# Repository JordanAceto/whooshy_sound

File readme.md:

# Effects pedal for making whooshy filter and phaser sweeping sounds

## This pedal accommodates various VCF plug-in boards, and contains rich modulation features.

### [SCHEMATIC](https://github.com/JordanAceto/whooshy_sound/blob/main/hardware/main_pcb/construction_docs/whooshy_sound_main_pcb_schematic.pdf)

---

### Features:
- Guitar pedal style stomp box.
- Can accept a wide variety of [filter plug-in boards](https://github.com/JordanAceto/VCF_plug_in_boards).
    - For guitars and other instrument-level signals I recommend starting with the "2164" filter plug-in boards, because these have very low noise and CV feedthrough.
    - Other plug-in boards will work for guitars, but may be a little noisier and thumpier than you wish. Try them out, they vary.
    - If you're using this in an effects loop or after a preamp, it doesn't matter as much and any of them will probably be fine.
- Manual frequency and resonance controls.
- Digitally generated LFO with morphing waveshaper, smoothly crossfades from triangle to sine to square to sample & hold.
- Analog envelope follower for when you want to quack and bwow instead of whoosh.

---

### Status of the project:

Revision | schematic | pcb layout | firmware | built and tested | safe to order boards
------|--------------|-----------|------------|---------|---------
0.1 | &#9745; | &#9745; | &#9745; | &#9745; | &#9745;

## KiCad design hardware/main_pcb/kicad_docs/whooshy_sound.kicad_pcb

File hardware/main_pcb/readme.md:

# Main PCB

## The main PCB contains:
- input and output audio buffers
- a software generated LFO
- an envelope follower
- a port which accepts various VCF plug-in boards
- power supply components

---

### PCB front view:

---

### PCB rear view:

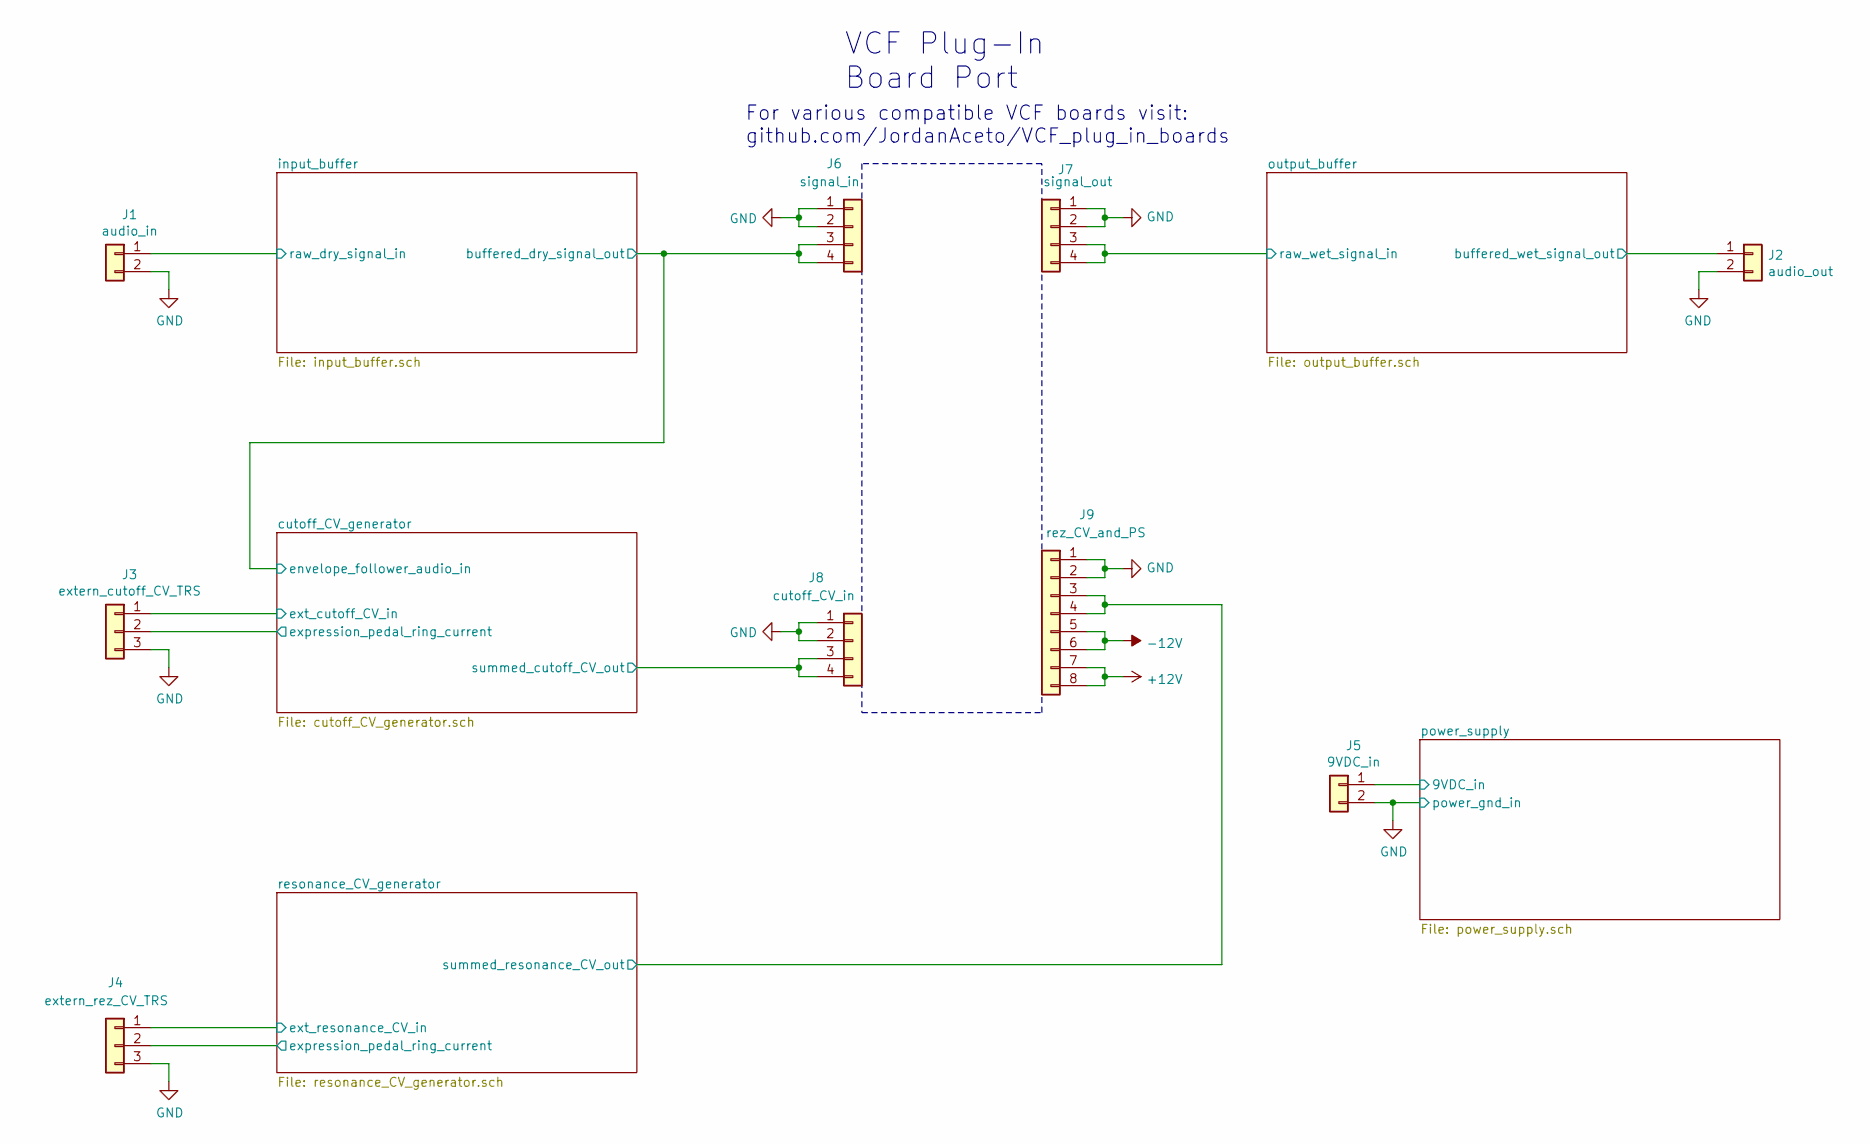
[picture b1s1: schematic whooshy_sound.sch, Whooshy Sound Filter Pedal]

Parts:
J1: audio_in; PinHeader_1x02_P2.54mm_Vertical
J2: audio_out; PinHeader_1x02_P2.54mm_Vertical
J3: extern_cutoff_CV_TRS; PinHeader_1x03_P2.54mm_Vertical
J4: extern_rez_CV_TRS; PinHeader_1x03_P2.54mm_Vertical
J5: 9VDC_in; PinHeader_1x02_P2.54mm_Vertical
J6: signal_in; PinSocket_1x04_P2.54mm_Vertical
J7: signal_out; PinSocket_1x04_P2.54mm_Vertical
J8: cutoff_CV_in; PinSocket_1x04_P2.54mm_Vertical
J9: rez_CV_and_PS; PinSocket_1x08_P2.54mm_Vertical

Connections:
+12V: J9.7, J9.8; also elsewhere on the board
-12V: J9.5, J9.6; also elsewhere on the board
/cutoff_CV_generator/expression_pedal_ring_current: J3.2; also elsewhere on the board
/cutoff_CV_generator/ext_cutoff_CV_in: J3.1; also elsewhere on the board
/cutoff_CV_generator/summed_cutoff_CV_out: J8.3, J8.4; also elsewhere on the board
/input_buffer/buffered_dry_signal_out: J6.3, J6.4; also elsewhere on the board
/input_buffer/raw_dry_signal_in: J1.1; also elsewhere on the board
/output_buffer/buffered_wet_signal_out: J2.1; also elsewhere on the board
/output_buffer/raw_wet_signal_in: J7.3, J7.4; also elsewhere on the board
/power_supply/9VDC_in: J5.1; also elsewhere on the board
/resonance_CV_generator/expression_pedal_ring_current: J4.2; also elsewhere on the board
/resonance_CV_generator/ext_resonance_CV_in: J4.1; also elsewhere on the board
/resonance_CV_generator/summed_resonance_CV_out: J9.3, J9.4; also elsewhere on the board
GND: J1.2, J2.2, J3.3, J4.3, J5.2, J6.1, J6.2, J7.1, J7.2, J8.1, J8.2, J9.1, J9.2; also elsewhere on the board

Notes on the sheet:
VCF Plug-In Board Port
For various compatible VCF boards visit: github.com/JordanAceto/VCF_plug_in_boards

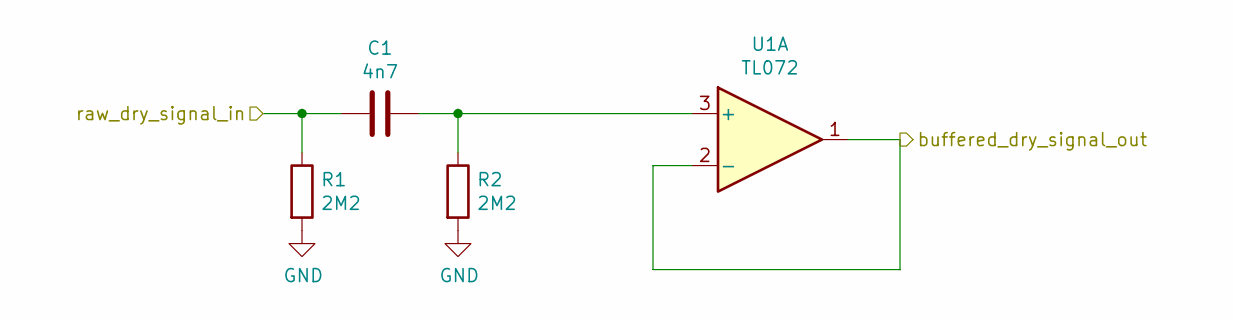
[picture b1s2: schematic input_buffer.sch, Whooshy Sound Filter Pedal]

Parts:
C1: 4n7; C_Rect_L7.0mm_W2.5mm_P5.00mm
R1, R2: 2M2; R_0805_2012Metric
U1: TL072; SOIC-8_3.9x4.9mm_P1.27mm

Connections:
/input_buffer/buffered_dry_signal_out: U1.1, U1.2 (-); also elsewhere on the board
/input_buffer/raw_dry_signal_in: C1.2, R1.1; also elsewhere on the board
GND: R1.2, R2.2; also elsewhere on the board
unnamed: C1.1, R2.1, U1.3 (+)

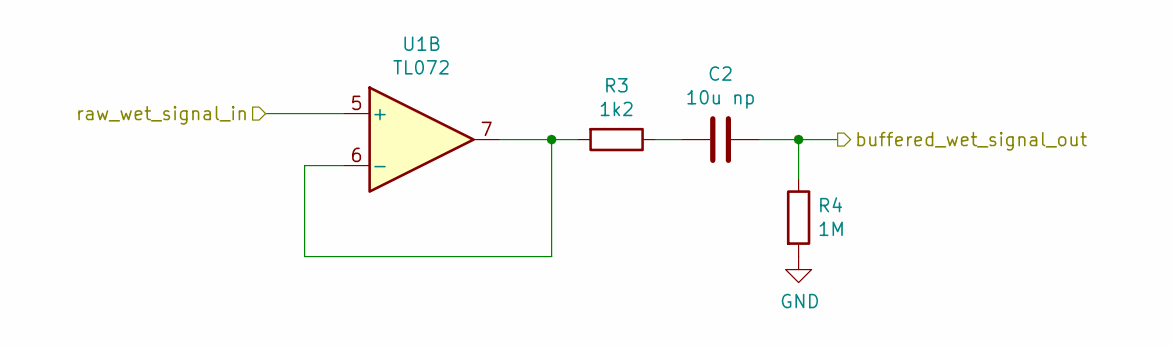
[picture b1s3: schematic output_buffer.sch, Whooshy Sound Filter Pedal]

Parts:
C2: 10u np; C_Radial_D6.3mm_H11.0mm_P2.50mm
R3: 1k2; R_0805_2012Metric
R4: 1M; R_0805_2012Metric
U1: TL072; SOIC-8_3.9x4.9mm_P1.27mm

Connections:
/output_buffer/buffered_wet_signal_out: C2.1, R4.1; also elsewhere on the board
/output_buffer/raw_wet_signal_in: U1.5 (+); also elsewhere on the board
GND: R4.2; also elsewhere on the board
unnamed: C2.2, R3.1
unnamed: R3.2, U1.6 (-), U1.7

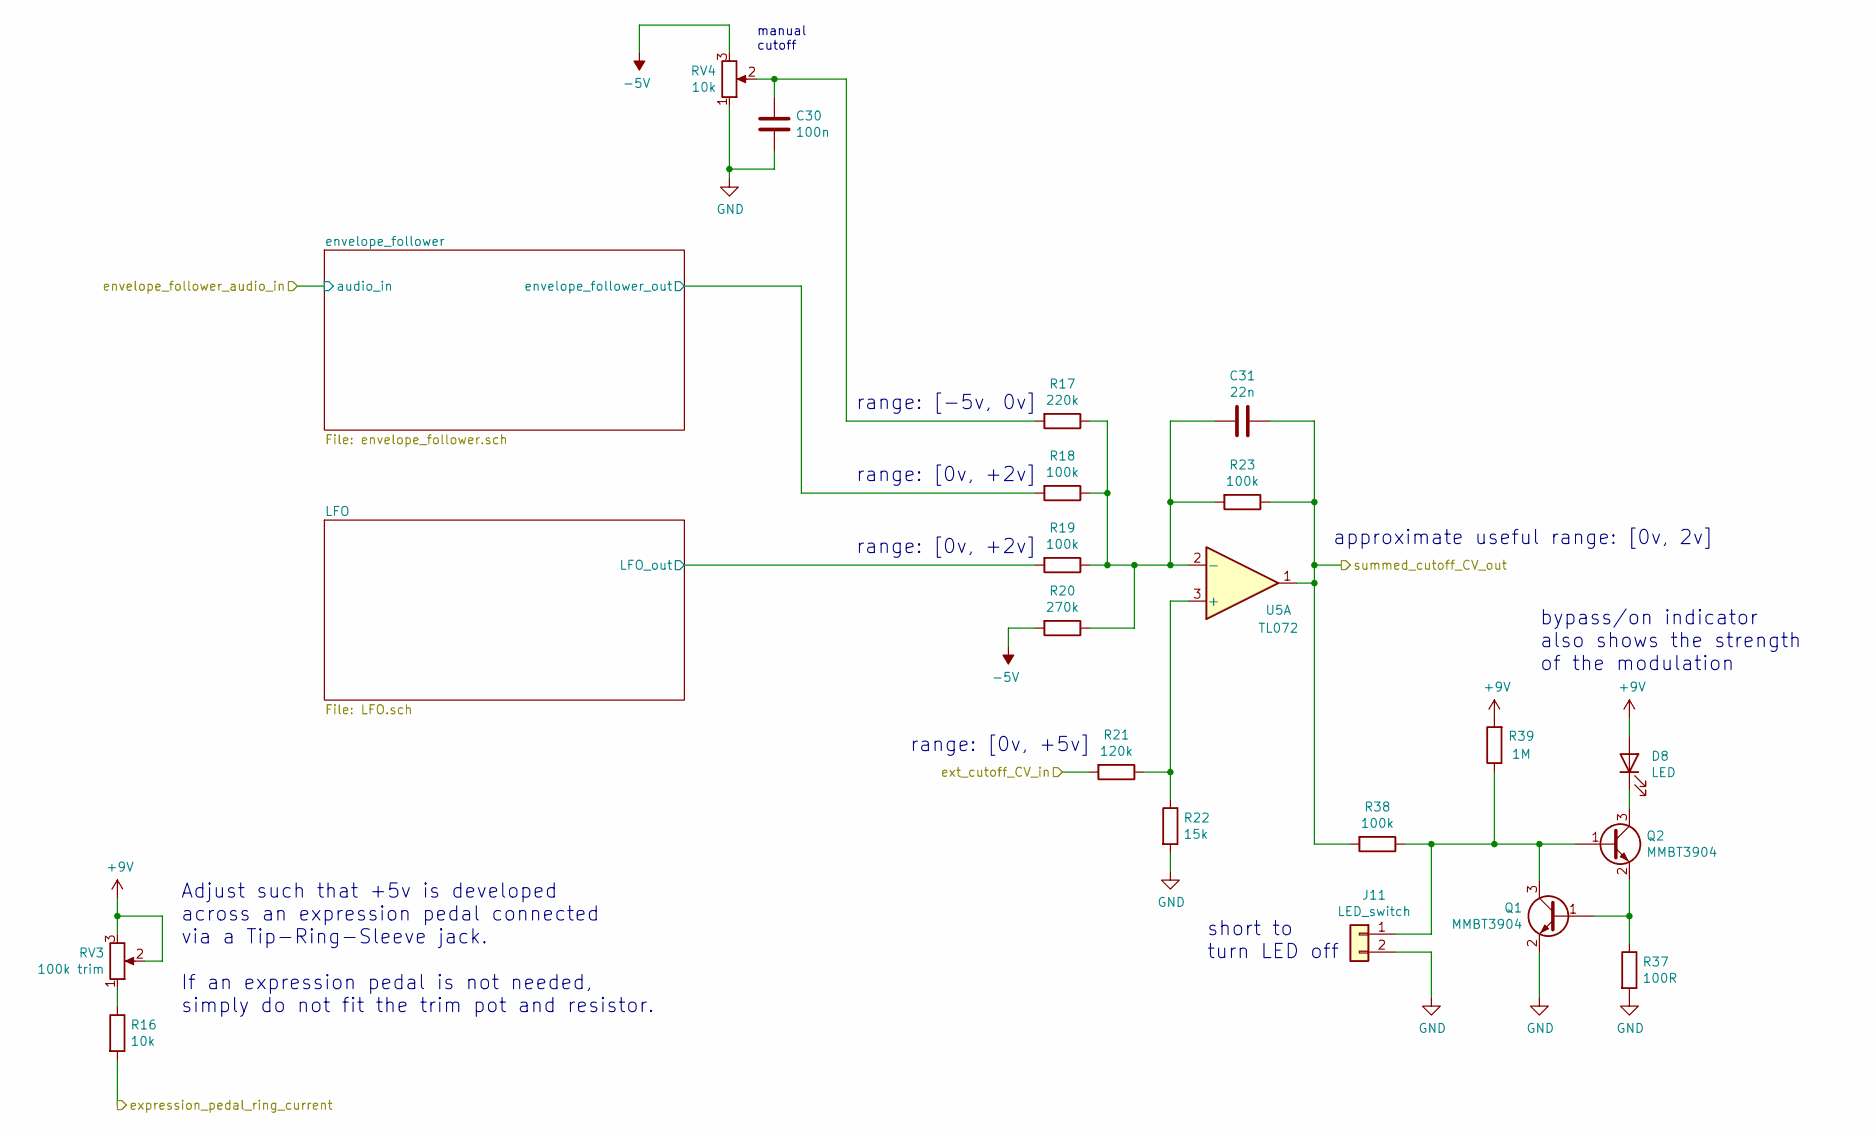
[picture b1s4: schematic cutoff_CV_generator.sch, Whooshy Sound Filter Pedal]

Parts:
C30: 100n; C_0805_2012Metric
C31: 22n; C_0805_2012Metric
D8: LED; LED_D5.0mm
J11: LED_switch; PinHeader_1x02_P2.54mm_Vertical
Q1, Q2: MMBT3904; SOT-23
R16: 10k; R_0805_2012Metric
R17: 220k; R_0805_2012Metric
R18, R19, R23, R38: 100k; R_0805_2012Metric
R20: 270k; R_0805_2012Metric
R21: 120k; R_0805_2012Metric
R22: 15k; R_0805_2012Metric
R37: 100R; R_0805_2012Metric
R39: 1M; R_0805_2012Metric
RV3: 100k trim; Potentiometer_Bourns_3296W_Vertical
RV4: 10k; Potentiometer_Alpha_RD901F-40-00D_Single_Vertical
U5: TL072; SOIC-8_3.9x4.9mm_P1.27mm

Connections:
+9V: D8.2 (A), R39.2, RV3.2, RV3.3; also elsewhere on the board
-5V: R20.2, RV4.3; also elsewhere on the board
/cutoff_CV_generator/LFO/LFO_out: R19.2; also elsewhere on the board
/cutoff_CV_generator/envelope_follower/envelope_follower_out: R18.2; also elsewhere on the board
/cutoff_CV_generator/expression_pedal_ring_current: R16.2; also elsewhere on the board
/cutoff_CV_generator/ext_cutoff_CV_in: R21.2; also elsewhere on the board
/cutoff_CV_generator/summed_cutoff_CV_out: C31.1, R23.1, R38.2, U5.1; also elsewhere on the board
GND: C30.2, J11.2, Q1.2 (E), R22.2, R37.2, RV4.1; also elsewhere on the board
unnamed: C30.1, R17.2, RV4.2
unnamed: C31.2, R17.1, R18.1, R19.1, R20.1, R23.2, U5.2 (-)
unnamed: D8.1 (K), Q2.3 (C)
unnamed: J11.1, Q1.3 (C), Q2.1 (B), R38.1, R39.1
unnamed: Q1.1 (B), Q2.2 (E), R37.1
unnamed: R16.1, RV3.1
unnamed: R21.1, R22.1, U5.3 (+)

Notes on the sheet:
range: [-5v, 0v]
range: [0v, +2v]
range: [0v, +5v]
approximate useful range: [0v, 2v]
manual cutoff
Adjust such that +5v is developed across an expression pedal connected via a Tip-Ring-Sleeve jack. If an expression pedal is not needed, simply do not fit the trim pot and resistor.
bypass/on indicator also shows the strength of the modulation
short to turn LED off

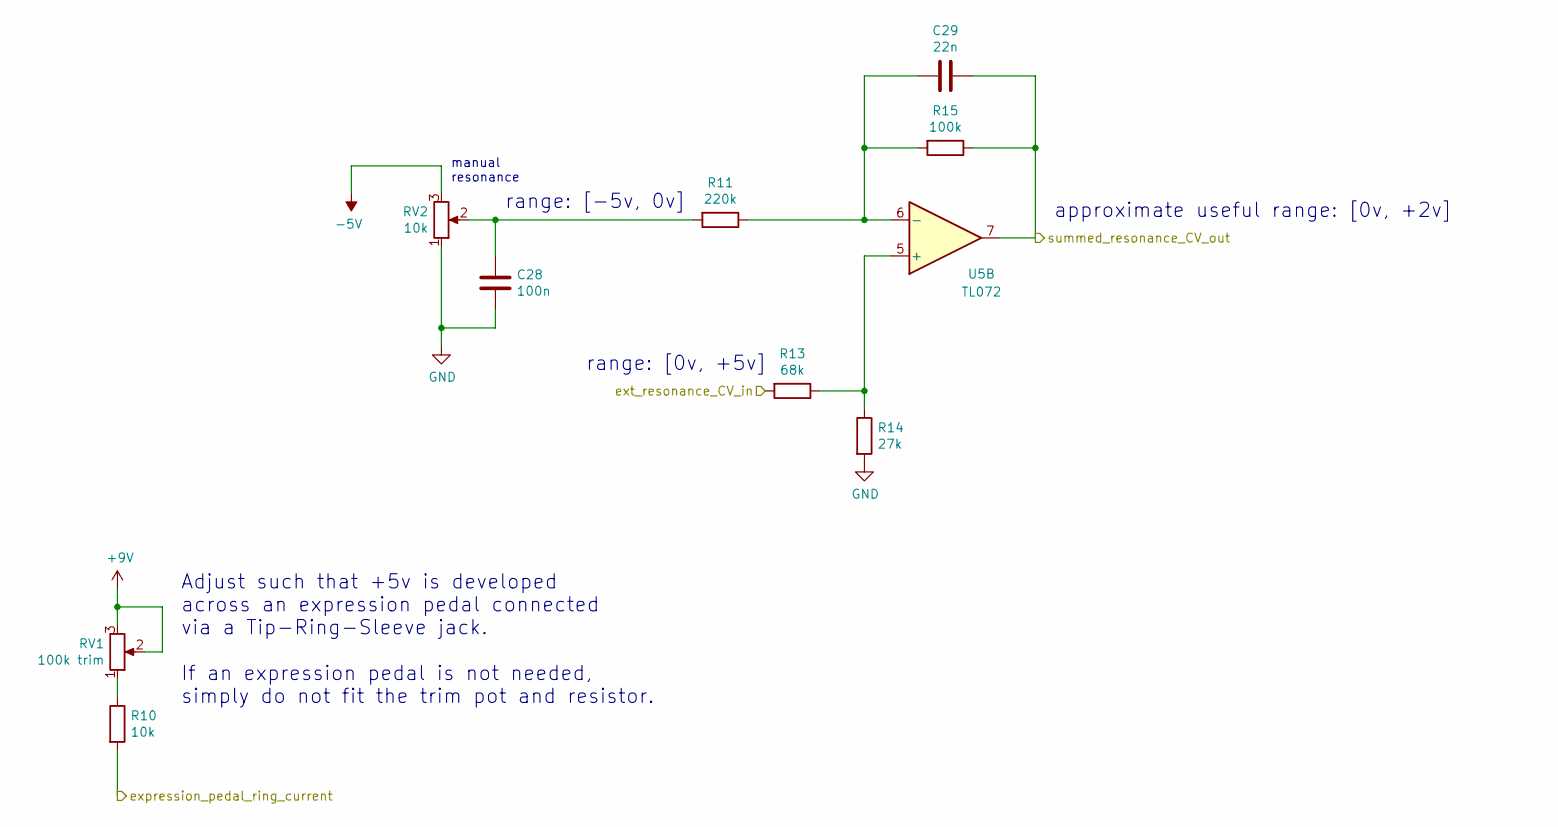
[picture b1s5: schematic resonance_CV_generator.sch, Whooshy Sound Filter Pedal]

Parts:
C28: 100n; C_0805_2012Metric
C29: 22n; C_0805_2012Metric
R10: 10k; R_0805_2012Metric
R11: 220k; R_0805_2012Metric
R13: 68k; R_0805_2012Metric
R14: 27k; R_0805_2012Metric
R15: 100k; R_0805_2012Metric
RV1: 100k trim; Potentiometer_Bourns_3296W_Vertical
RV2: 10k; Potentiometer_Alpha_RD901F-40-00D_Single_Vertical
U5: TL072; SOIC-8_3.9x4.9mm_P1.27mm

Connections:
+9V: RV1.2, RV1.3; also elsewhere on the board
-5V: RV2.3; also elsewhere on the board
/resonance_CV_generator/expression_pedal_ring_current: R10.2; also elsewhere on the board
/resonance_CV_generator/ext_resonance_CV_in: R13.2; also elsewhere on the board
/resonance_CV_generator/summed_resonance_CV_out: C29.1, R15.1, U5.7; also elsewhere on the board
GND: C28.2, R14.2, RV2.1; also elsewhere on the board
unnamed: C28.1, R11.2, RV2.2
unnamed: C29.2, R11.1, R15.2, U5.6 (-)
unnamed: R10.1, RV1.1
unnamed: R13.1, R14.1, U5.5 (+)

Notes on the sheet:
approximate useful range: [0v, +2v]
range: [-5v, 0v]
range: [0v, +5v]
Adjust such that +5v is developed across an expression pedal connected via a Tip-Ring-Sleeve jack. If an expression pedal is not needed, simply do not fit the trim pot and resistor.
manual resonance

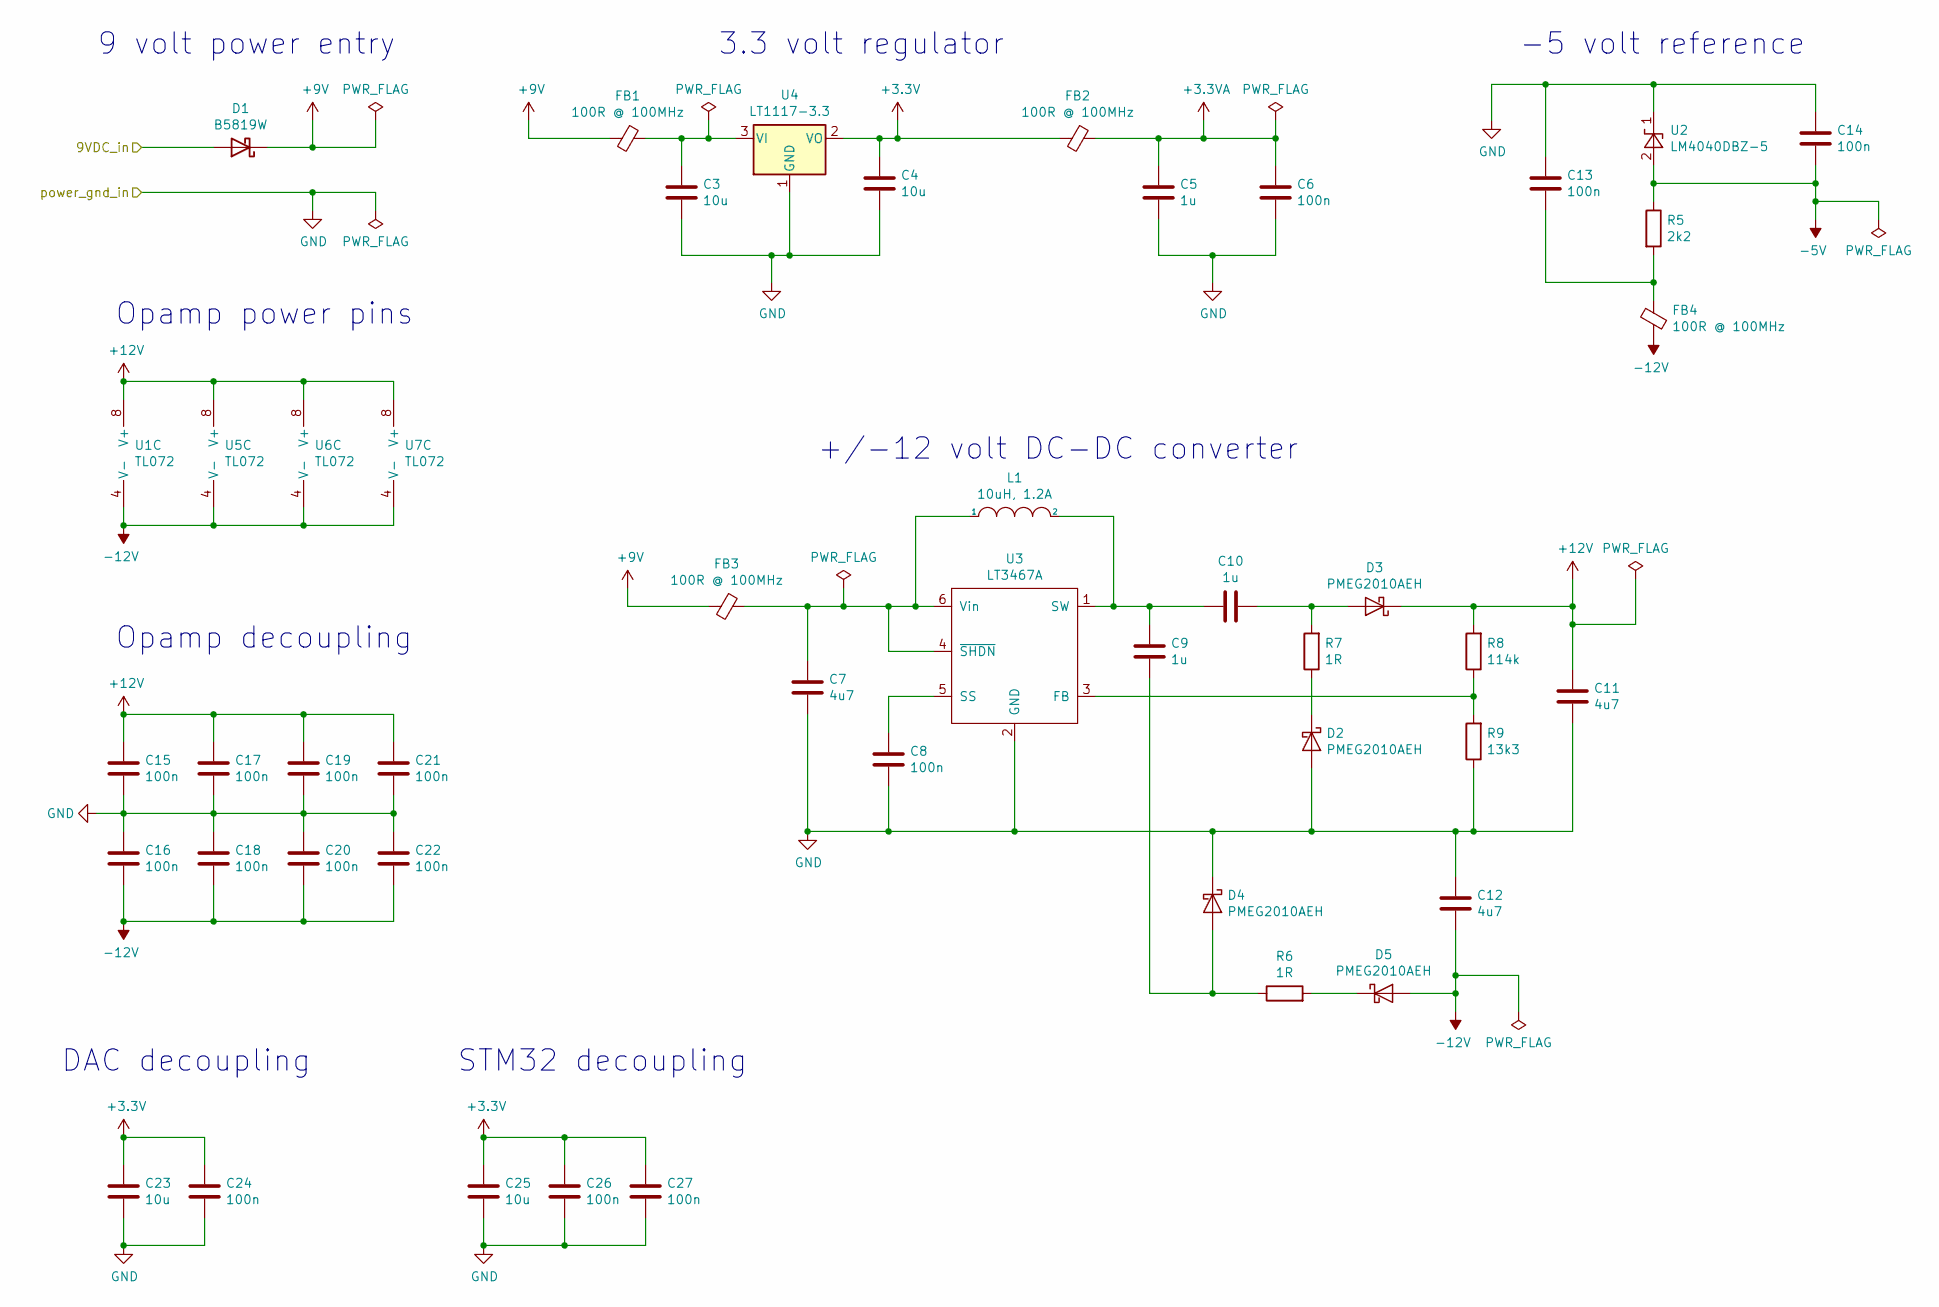
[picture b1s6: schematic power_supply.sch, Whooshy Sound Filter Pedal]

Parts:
C3, C4, C23, C25: 10u; C_0805_2012Metric
C5, C9, C10: 1u; C_0805_2012Metric
C6, C8, C13, C14, C15, C16, C17, C18, C19, C20, C21, C22, C24, C26, C27: 100n; C_0805_2012Metric
C7, C11, C12: 4u7; C_0805_2012Metric
D1: B5819W; D_SOD-123
D2, D3, D4, D5: PMEG2010AEH; D_SOD-123F
FB1, FB2, FB3, FB4: 100R @ 100MHz; L_0805_2012Metric
L1: 10uH, 1.2A; L_Taiyo-Yuden_NR-50xx
R5: 2k2; R_0805_2012Metric
R6, R7: 1R; R_0805_2012Metric
R8: 114k; R_0805_2012Metric
R9: 13k3; R_0805_2012Metric
U1, U5, U6, U7: TL072; SOIC-8_3.9x4.9mm_P1.27mm
U2: LM4040DBZ-5; SOT-23
U3: LT3467A; TSOT-23-6
U4: LT1117-3.3; SOT-223-3_TabPin2

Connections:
+3.3VA: C5.1, C6.1, FB2.1; also elsewhere on the board
+3V3: C4.1, C23.1, C24.1, C25.1, C26.1, C27.1, FB2.2, U4.2 (VO); also elsewhere on the board
+9V: D1.1 (K), FB1.2, FB3.2; also elsewhere on the board
+12V: C11.1, C15.1, C17.1, C19.1, C21.1, D3.1 (K), R8.2, U1.8 (V+), U5.8 (V+), U6.8 (V+), U7.8 (V+); also elsewhere on the board
-5V: C14.2, R5.1, U2.2 (A); also elsewhere on the board
-12V: C12.2, C16.2, C18.2, C20.2, C22.2, D5.2 (A), FB4.1, U1.4 (V-), U5.4 (V-), U6.4 (V-), U7.4 (V-); also elsewhere on the board
/power_supply/9VDC_in: D1.2 (A); also elsewhere on the board
GND: C3.2, C4.2, C5.2, C6.2, C7.2, C8.2, C11.2, C12.1, C13.1, C14.1, C15.2, C16.1, C17.2, C18.1, C19.2, C20.1, C21.2, C22.1, C23.2, C24.2, C25.2, C26.2, C27.2, D2.2 (A), D4.1 (K), R9.1, U2.1 (K), U3.2 (GND), U4.1 (GND); also elsewhere on the board
unnamed: C3.1, FB1.1, U4.3 (VI)
unnamed: C7.1, FB3.1, L1.1, U3.4 (~SHDN), U3.6 (Vin)
unnamed: C8.1, U3.5 (SS)
unnamed: C9.2, D4.2 (A), R6.1
unnamed: C10.1, D3.2 (A), R7.2
unnamed: C9.1, C10.2, L1.2, U3.1 (SW)
unnamed: C13.2, FB4.2, R5.2
unnamed: D2.1 (K), R7.1
unnamed: D5.1 (K), R6.2
unnamed: R8.1, R9.2, U3.3 (FB)

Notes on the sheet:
-5 volt reference
+/-12 volt DC-DC converter
3.3 volt regulator
9 volt power entry
Opamp decoupling
DAC decoupling
STM32 decoupling
Opamp power pins

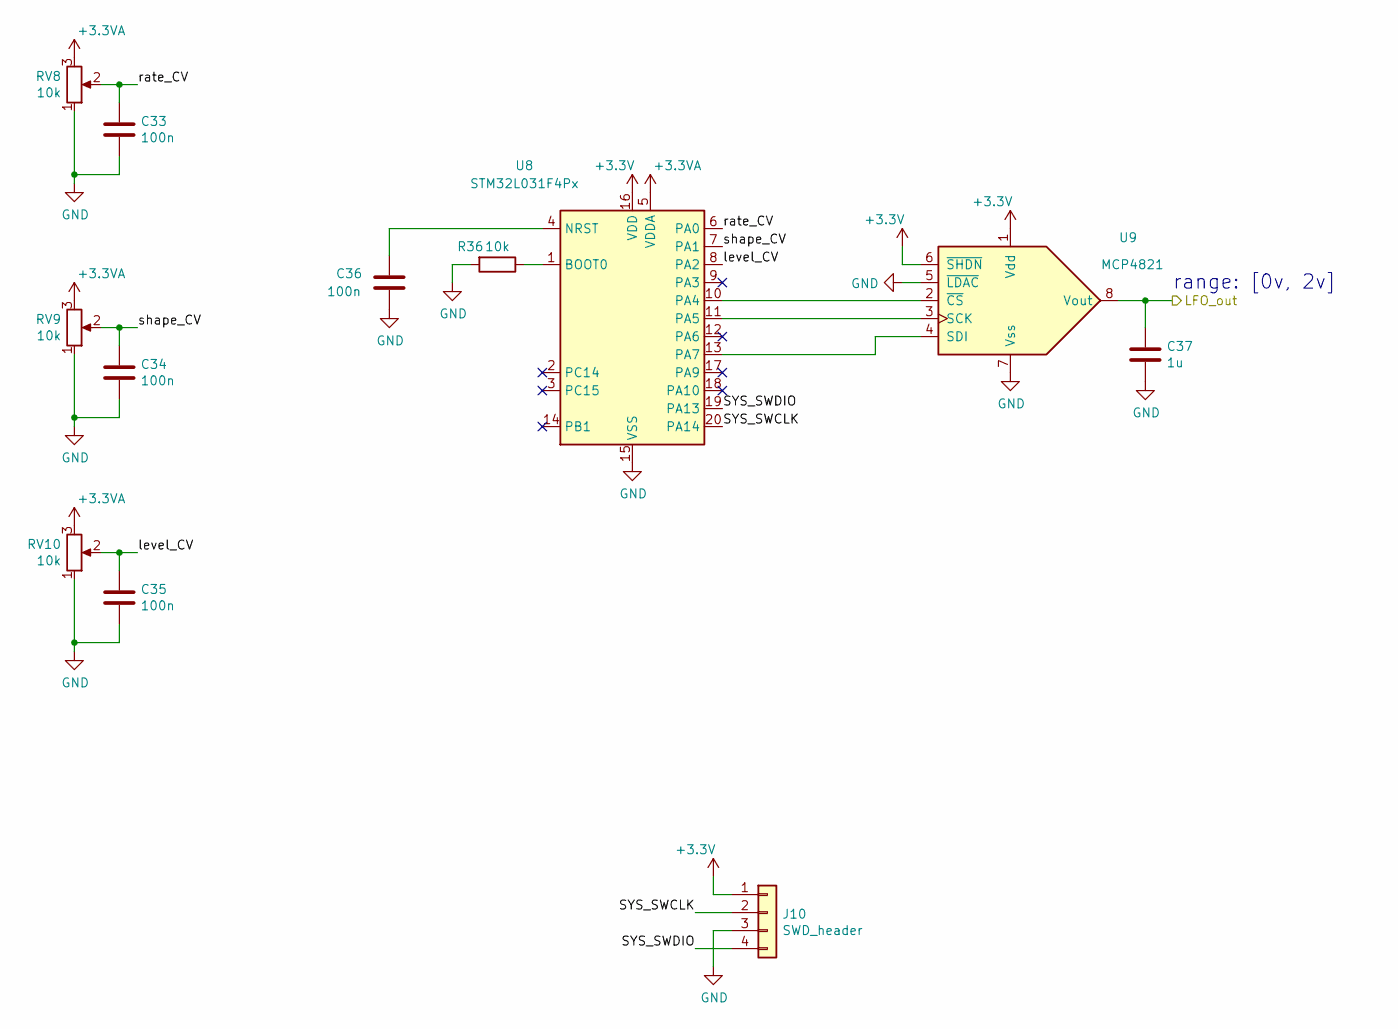
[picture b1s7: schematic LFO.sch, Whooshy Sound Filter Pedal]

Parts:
C33, C34, C35, C36: 100n; C_0805_2012Metric
C37: 1u; C_0805_2012Metric
J10: SWD_header; PinHeader_1x04_P2.54mm_Vertical
R36: 10k; R_0805_2012Metric
RV8, RV9, RV10: 10k; Potentiometer_Alpha_RD901F-40-00D_Single_Vertical
U8: STM32L031F4Px; TSSOP-20_4.4x6.5mm_P0.65mm
U9: MCP4821; MSOP-8_3x3mm_P0.65mm

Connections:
+3.3VA: RV8.3, RV9.3, RV10.3, U8.5 (VDDA); also elsewhere on the board
+3V3: J10.1, U8.16 (VDD), U9.1 (Vdd), U9.6 (~SHDN); also elsewhere on the board
/cutoff_CV_generator/LFO/LFO_out: C37.1, U9.8 (Vout); also elsewhere on the board
/cutoff_CV_generator/LFO/SYS_SWCLK: J10.2, U8.20 (PA14)
/cutoff_CV_generator/LFO/SYS_SWDIO: J10.4, U8.19 (PA13)
/cutoff_CV_generator/LFO/level_CV: C35.1, RV10.2, U8.8 (PA2)
/cutoff_CV_generator/LFO/rate_CV: C33.1, RV8.2, U8.6 (PA0)
/cutoff_CV_generator/LFO/shape_CV: C34.1, RV9.2, U8.7 (PA1)
GND: C33.2, C34.2, C35.2, C36.2, C37.2, J10.3, R36.2, RV8.1, RV9.1, RV10.1, U8.15 (VSS), U9.5 (~LDAC), U9.7 (Vss); also elsewhere on the board
unnamed: C36.1, U8.4 (NRST)
unnamed: R36.1, U8.1 (BOOT0)
unnamed: U8.10 (PA4), U9.2 (~CS)
unnamed: U8.11 (PA5), U9.3 (SCK)
unnamed: U8.13 (PA7), U9.4 (SDI)

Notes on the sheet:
range: [0v, 2v]

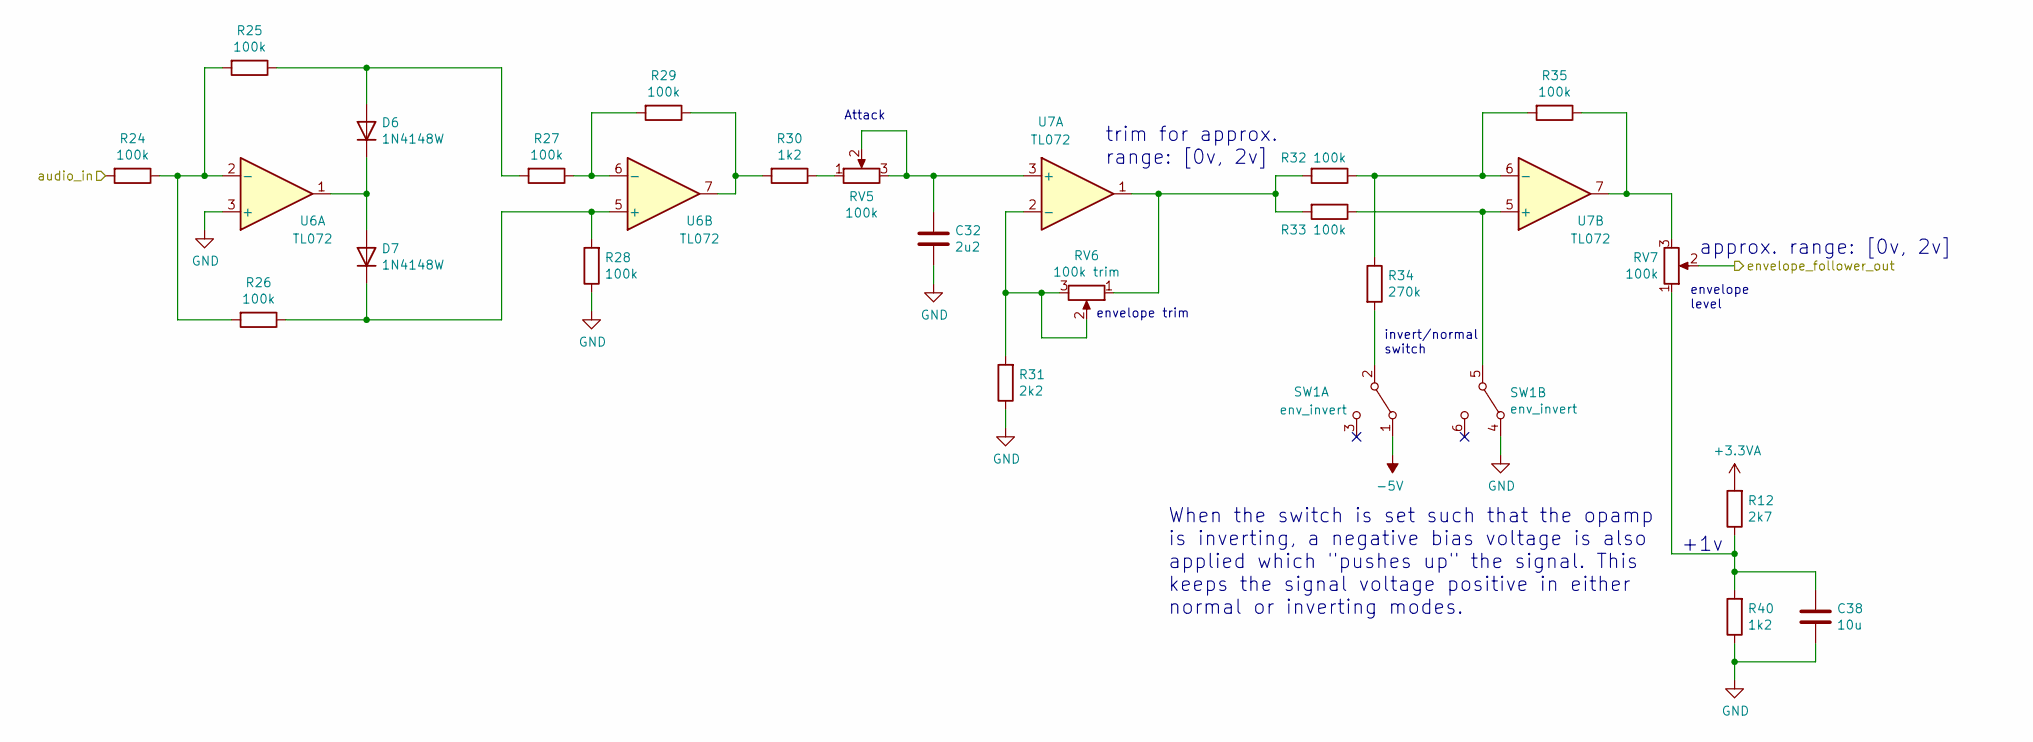
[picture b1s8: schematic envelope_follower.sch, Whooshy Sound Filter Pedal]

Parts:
C32: 2u2; C_0805_2012Metric
C38: 10u; C_0805_2012Metric
D6, D7: 1N4148W; D_SOD-123
R12: 2k7; R_0805_2012Metric
R24, R25, R26, R27, R28, R29, R32, R33, R35: 100k; R_0805_2012Metric
R30, R40: 1k2; R_0805_2012Metric
R31: 2k2; R_0805_2012Metric
R34: 270k; R_0805_2012Metric
RV5, RV7: 100k; Potentiometer_Alpha_RD901F-40-00D_Single_Vertical
RV6: 100k trim; Potentiometer_Bourns_3296W_Vertical
SW1: env_invert; DPDT_on_on
U6, U7: TL072; SOIC-8_3.9x4.9mm_P1.27mm

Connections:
+3.3VA: R12.2; also elsewhere on the board
-5V: SW1.1 (A); also elsewhere on the board
/cutoff_CV_generator/envelope_follower/envelope_follower_out: RV7.2; also elsewhere on the board
/input_buffer/buffered_dry_signal_out: R24.2; also elsewhere on the board
GND: C32.2, C38.2, R28.1, R31.1, R40.1, SW1.4 (A), U6.3 (+); also elsewhere on the board
unnamed: C32.1, RV5.2, RV5.3, U7.3 (+)
unnamed: C38.1, R12.1, R40.2, RV7.1
unnamed: D6.1 (K), D7.2 (A), U6.1
unnamed: D6.2 (A), R25.1, R27.2
unnamed: D7.1 (K), R26.1, R28.2, U6.5 (+)
unnamed: R24.1, R25.2, R26.2, U6.2 (-)
unnamed: R27.1, R29.2, U6.6 (-)
unnamed: R29.1, R30.2, U6.7
unnamed: R30.1, RV5.1
unnamed: R31.2, RV6.2, RV6.3, U7.2 (-)
unnamed: R32.1, R34.1, R35.2, U7.6 (-)
unnamed: R32.2, R33.2, RV6.1, U7.1
unnamed: R33.1, SW1.5 (B), U7.5 (+)
unnamed: R34.2, SW1.2 (B)
unnamed: R35.1, RV7.3, U7.7

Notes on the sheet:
Attack
envelope trim
trim for approx. range: [0v, 2v]
envelope level
When the switch is set such that the opamp is inverting, a negative bias voltage is also applied which "pushes up" the signal. This keeps the signal voltage positive in either normal or inverting modes.
invert/normal switch
approx. range: [0v, 2v]
+1v

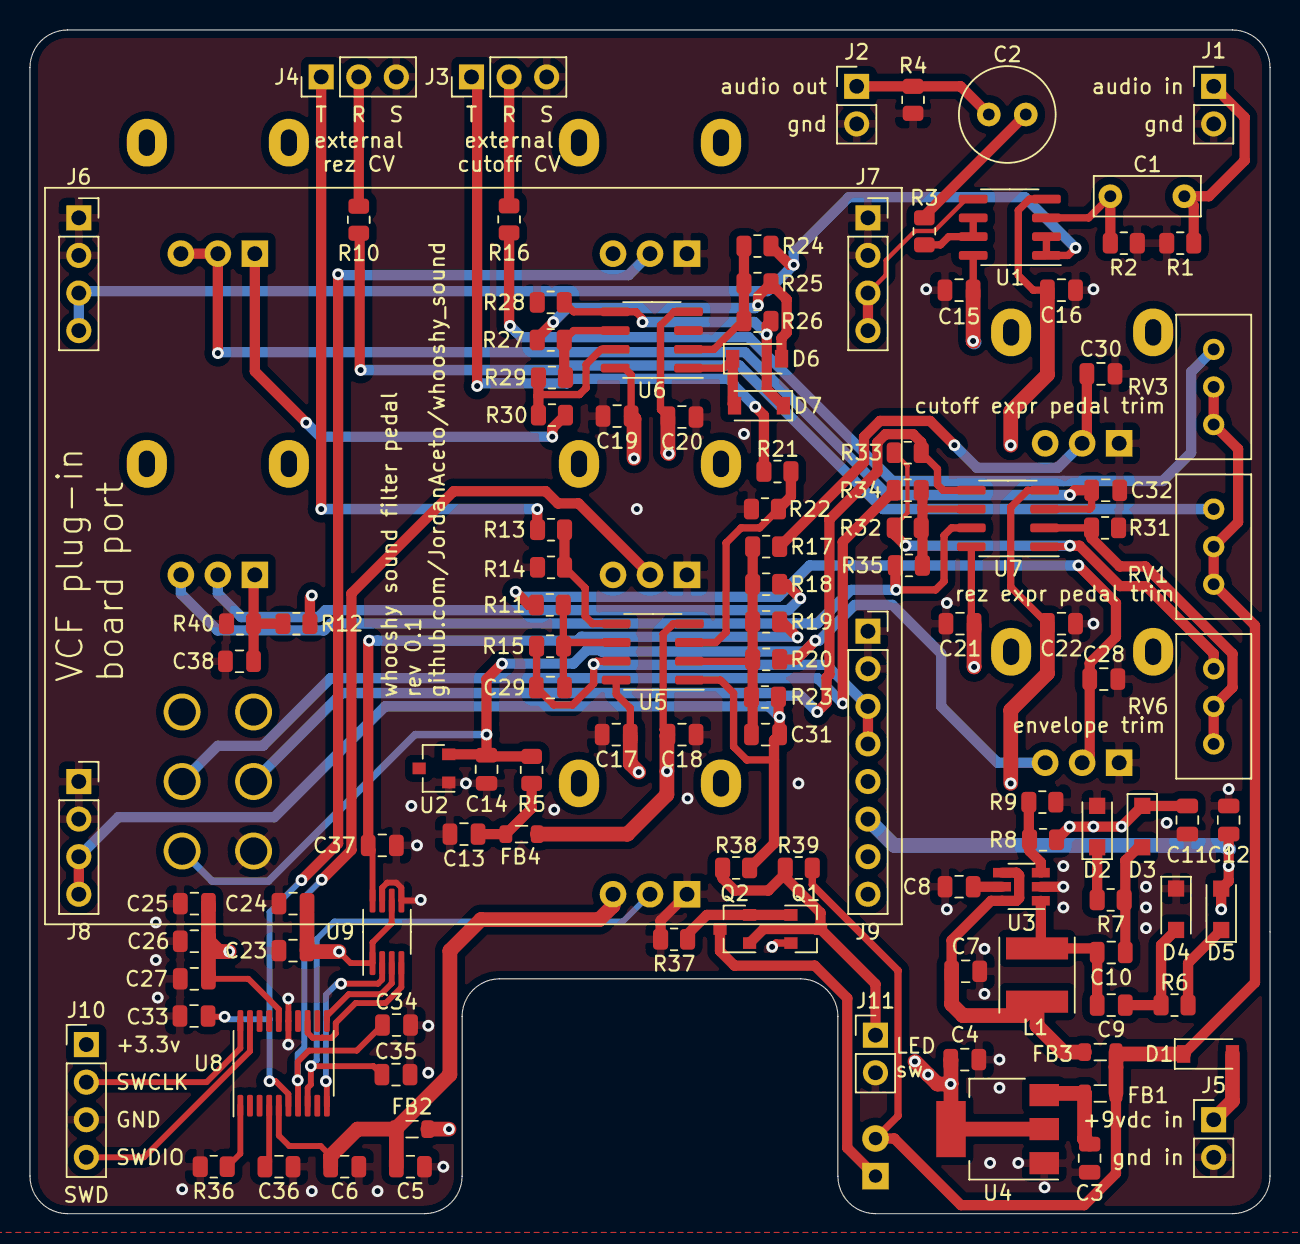
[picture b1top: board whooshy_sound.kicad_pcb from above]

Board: 4 copper layers, 83.8 x 80.0 mm, 124 parts (0 on the bottom side), 69 nets.

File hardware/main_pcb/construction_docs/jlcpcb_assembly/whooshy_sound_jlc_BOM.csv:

Comment,Designator,Footprint,LCSC Part Number
TL072,"U7,U6,U5,U1",SOIC-8_3.9x4.9_1.27P,C6961
1k2,"R40, R3, R30",0805,C17379
2k7,R12,0805,C17530
1M,"R39,R4",0805,C17514
100k,"R38,R35,R33,R32,R29,R28,R27,R26,R25,R24,R23,R19,R18,R15",0805,C17407
100R,R37,0805,C17408
MMBT3904,"Q2,Q1",SOT-23-3,C20526
10k,"R36,R16,R10",0805,C17414
270k,"R34, R20",0805,C17589
2k2,"R31,R5",0805,C17520
15k,R22,0805,C17475
120k,R21,0805,C17436
68k,R13,0805,C17801
220k,"R17,R11",0805,C17556
27k,R14,0805,C17593
1R,"R7,R6",0805,C25271
2M2,"R2,R1",0805,C26113
Bead,"FB4,FB3,FB2,FB1",0805,C1015
1N4148W,"D7,D6",SOD-123,C81598
B5819W,D1,SOD-123,C8598
1u,"C37,C10,C9,C5",0805,C28323
100n,"C36,C35,C34,C33,C30,C28,C27,C26,C24,C22,C21,C20,C19,C18,C17,C16,C15,C14,C13,C8,C6",0805,C49678
2u2,C32,0805,C49217
22n,"C31,C29",0805,C1729
10u,"C38, C25,C23,C4,C3",0805,C15850
4u7,"C12,C11,C7",0805,C1779

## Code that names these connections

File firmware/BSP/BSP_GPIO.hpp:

#pragma once

/** @brief General Purpose Input Output pins */
namespace BSP::gpio
{
    /**
     * @brief Initialize the GPIO pins.
     *
     * PA0 is an analog input mapped to the rate CV input.
     * PA1 is an analog input mapped to the shape CV input.
     * PA2 is an analog input mapped to the level CV input.
     *
     * PA4 is SPI1 NSS DAC chip select.
     * PA5 is SPI1 SCK.
     * PA7 is SPI1 MOSI
     *
     * PA13 is SYS SWDIO
     * PA14 is SYS SWCLK
     */
    void init(void);
}

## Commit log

2021-06-18 rough schematic and layout done
2021-06-18 add datasheets
2021-06-18 tweak pcb
2021-06-19 add license
2021-06-19 start front panel
2021-06-19 move main pcb into its own dir
2021-06-19 start drill guides
2021-06-19 start jack panel
2021-06-19 add rendered pic
2021-06-19 add placeholder readmes so that dir structure is tracked
2021-06-19 add enclosure specs
2021-06-25 add files, do simple blinky hello world
2021-06-25 fix 0ff-by-one systick bug
2021-06-25 use initialization constant for GPIOA moder
2021-06-25 add and demo SPI
2021-06-26 change sine LUT to int
2021-06-26 split LUTs into .h and .c files
2021-06-26 add LFO module, do simple LFO test in main
2021-06-26 add PRNG module, impl random waveshaper, demo in main
2021-06-26 implement LFO wave crossfader
2021-06-26 add python trapezoid visualization script
2021-06-27 make LUT declarations extern
2021-06-27 increase warnings, catch i/ui comparison op
2021-06-27 change expo map LUT from float to uint
2021-06-27 add RCC definition for sys core clock freq
2021-06-27 change scheduling method
2021-06-27 fix issue with LFO random wave
2021-06-27 get ADC working and demo
2021-06-27 move DMA module to BSP
2021-06-28 add VCF plug-in boards submodule
2021-06-28 add LED driver, change LED to 5mm
2021-06-28 regenerate BOM and schem
2021-06-29 tidy up main board
2021-06-29 update main pcb pics
2021-06-29 update main board schematic
2021-06-29 generate gerbers
2021-06-29 change LFO signals to signed, implement volume control
2021-06-29 LFO waves are now signed ints
2021-06-29 add drill guides
2021-06-29 add panel gerbers
2021-06-30 flip env invert switch, condense cap types
2021-06-30 generate jlc pcb assembly docs
2021-06-30 regenerate gerbers
2021-06-30 typo in docstring
2021-07-01 flesh out firmware readme
2021-07-01 work on main readme
2021-07-01 reduce font size
2021-07-01 hardware readme
2021-07-01 add offboard wiring diagram
2021-07-03 add warning note to readme
2021-07-06 add smt assembly readme
2021-07-12 update drill guides
2021-07-14 use correct ADC inputs
2021-07-20 change DAC to MCP4821
2021-07-26 change firmware from c to c++
2021-07-26 use ADC hardware oversampling
2021-08-05 center envelope follower around +1v, tidy up
2021-08-14 change timing of random wave
2021-08-14 tweak LFO frequency range
2021-12-26 remove warning
2022-01-05 add pics, update readme
2022-01-05 add link to schematic
2022-01-16 update vcf boards ref

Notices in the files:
hardware/kicad_docs/LFO.sch:
creativecommons.org/licenses/by/4.0
Licencse: CC by 4.0
hardware/kicad_docs/whooshy_sound.sch:
License: CC by 4.0
